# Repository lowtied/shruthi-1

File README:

Shruthi-1, a digital/analog hybrid MIDI monosynth.

This project is a redesign of the original Shruti-1, with a spec'ed up CPU,
and a focus on easy upgrades/modification of the analog section.
The ATMega644p allows new features in the firmware -- a larger selection of
oscillator algorithms, a bigger selection of wavetables, and a tiny sequencer.

Original developer: Emilie Gillet (emilie.o.gillet@gmail.com)

The firmware is released under a GPL3.0 license. It includes a
reimplementation of the formant synthesis algorithm used in Peter Knight's
Cantarino speech synthesizer.

The PCB layouts and schematics (in /hardware/shruthi/design/pcb)
are released under a Creative Commons cc-by-sa 3.0 license - except for some
discontinued filter boards which were released under a cc-by-nc-sa 3.0 license.

Documentation, analyses, simulations and 3D models are released under a
Creative Commons cc-by-sa 3.0 license.

PCB art:
- "saraswati" by Francois Barbut.
- "peacock_face" by Emilie Gillet.
- "radha" by Emilie Gillet.

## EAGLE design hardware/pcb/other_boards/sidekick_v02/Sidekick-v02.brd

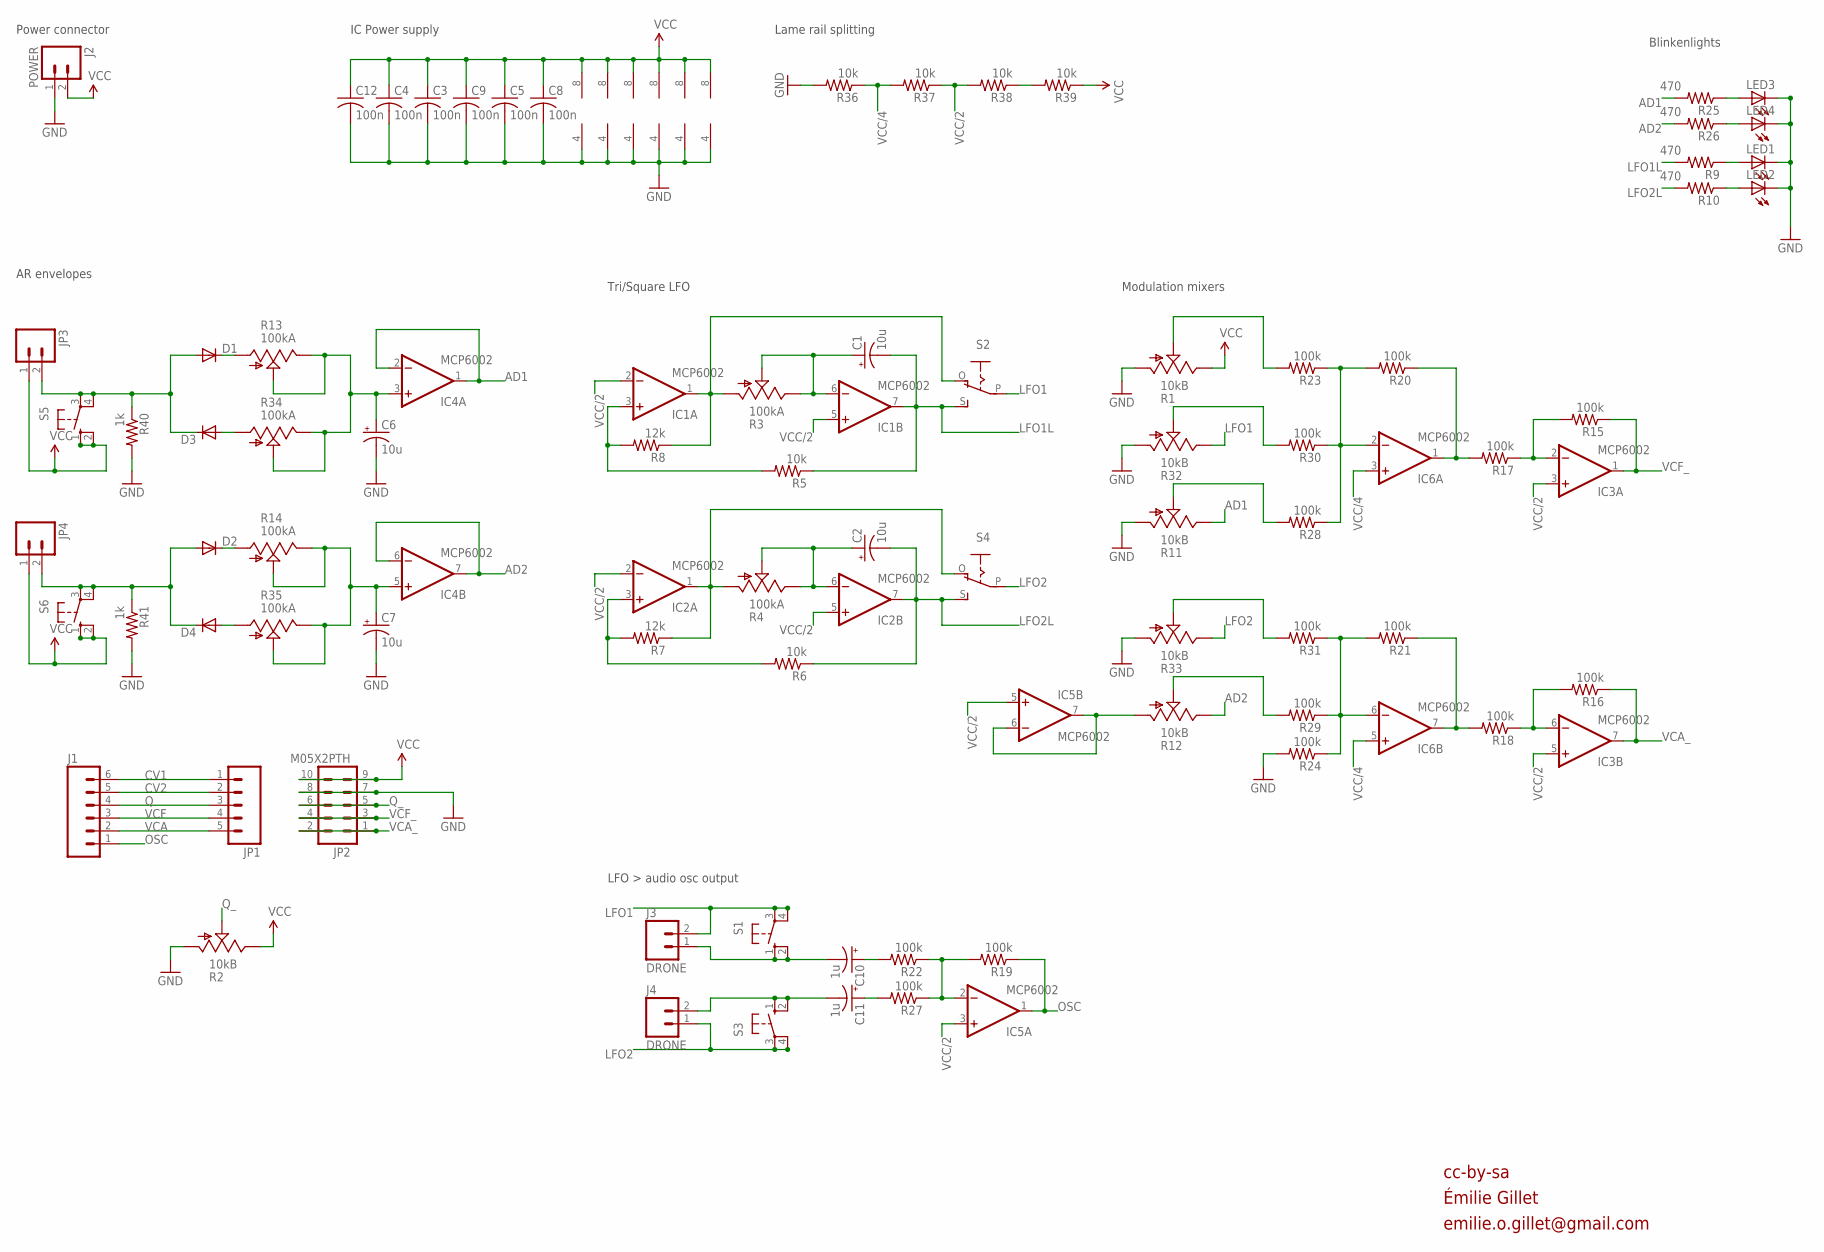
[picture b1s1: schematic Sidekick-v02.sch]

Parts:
C1, C2, C6, C7: 10u; E2,5-6
C3, C4, C5, C8, C9, C12: 100n; C025-024X044
C10, C11: 1u; E2,5-6
D1, D2, D3, D4: DIODE-D-5; D-5
IC1, IC2, IC3, IC4, IC5, IC6: MCP6002; DIL08
J1: M06SIP; 1X06
J2: POWER; 1X02
J3, J4: DRONE; 1X02
JP1: M05PTH; 1X05
JP2: M05X2PTH; AVR_ICSP
JP3, JP4: M02; 1X02_LONGPADS
LED1, LED2, LED3, LED4: LED3MM
R1, R2, R11, R12, R32, R33: 10kB; ALPS_POT_SFE
R3, R4, R13, R14, R34, R35: 100kA; ALPS_POT_SFE
R5, R6, R36, R37, R38, R39: 10k; 0204/7
R7, R8: 12k; 0204/7
R9, R10, R25, R26: 470; 0204/7
R15, R16, R17, R18, R19, R20, R21, R22, R23, R24, R27, R28, R29, R30, R31: 100k; 0204/7
R40, R41: 1k; 0204/7
S1, S3, S5, S6: 40-XX; B3F-40XX
S2, S4: EG1218S; EG1218

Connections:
AD1: IC4.1 (OUT), IC4.2 (-IN), R11.P$1 (E), R25.2
AD2: IC4.6 (-IN), IC4.7 (OUT), R12.P$1 (E), R26.2
CV1: J1.6, JP1.1
CV2: J1.5, JP1.2
GND: C3.2, C4.2, C5.2, C6.-, C7.-, C8.2, C9.2, C12.2, IC1.4 (V-), IC2.4 (V-), IC3.4 (V-), IC4.4 (V-), IC5.4 (V-), IC6.4 (V-), J2.1, JP2.7, JP2.8, LED1.K (C), LED2.K (C), LED3.K (C), LED4.K (C), R1.P$3 (A), R2.P$3 (A), R11.P$3 (A), R24.2, R32.P$3 (A), R33.P$3 (A), R36.2, R40.2, R41.2
LFO1: J3.2, R32.P$1 (E), S1.3, S1.4 (P1), S2.P
LFO1L: C1.-, IC1.7 (OUT), R5.1, R9.2, S2.S
LFO2: J4.1, R33.P$1 (E), S3.3, S3.4 (P1), S4.P
LFO2L: C2.-, IC2.7 (OUT), R6.1, R10.2, S4.S
unnamed: C11.-, J4.2, S3.1 (S), S3.2 (S1)
unnamed: D1.C, R13.P$3 (A)
unnamed: D3.A, R34.P$3 (A)
unnamed: R30.2, R32.P$2 (S)
unnamed: D2.C, R14.P$3 (A)
unnamed: D4.A, R35.P$3 (A)
unnamed: C6.+, IC4.3 (+IN), R13.P$1 (E), R13.P$2 (S), R34.P$1 (E), R34.P$2 (S)
unnamed: C7.+, IC4.5 (+IN), R14.P$1 (E), R14.P$2 (S), R35.P$1 (E), R35.P$2 (S)
unnamed: IC6.2 (-IN), R20.2, R23.1, R28.1, R30.1
unnamed: D1.A, D3.C, JP3.2, R40.1, S5.3, S5.4 (P1)
unnamed: D2.A, D4.C, JP4.2, R41.1, S6.3, S6.4 (P1)
unnamed: C1.+, IC1.6 (-IN), R3.P$1 (E), R3.P$2 (S)
unnamed: LED3.A, R25.1
unnamed: LED4.A, R26.1
unnamed: R1.P$2 (S), R23.2
unnamed: R11.P$2 (S), R28.2
unnamed: IC6.1 (OUT), R17.2, R20.1
unnamed: IC3.2 (-IN), R15.2, R17.1
unnamed: IC6.6 (-IN), R21.2, R24.1, R29.1, R31.1
unnamed: R31.2, R33.P$2 (S)
unnamed: R12.P$2 (S), R29.2
unnamed: IC1.3 (+IN), R5.2, R8.2
unnamed: IC6.7 (OUT), R18.2, R21.1
unnamed: IC3.6 (-IN), R16.2, R18.1
unnamed: IC1.1 (OUT), R3.P$3 (A), R8.1, S2.O
unnamed: IC2.3 (+IN), R6.2, R7.2
unnamed: C2.+, IC2.6 (-IN), R4.P$1 (E), R4.P$2 (S)
unnamed: IC2.1 (OUT), R4.P$3 (A), R7.1, S4.O
unnamed: IC5.2 (-IN), R19.2, R22.1, R27.1
unnamed: LED1.A, R9.1
unnamed: R38.1, R39.2
unnamed: LED2.A, R10.1
unnamed: C11.+, R27.2
unnamed: C10.+, R22.2
unnamed: C10.-, J3.1, S1.1 (S), S1.2 (S1)
NETX: IC5.6 (-IN), IC5.7 (OUT), R12.P$3 (A)
OSC: IC5.1 (OUT), J1.1, R19.1
Q: J1.4, JP1.3
Q_: JP2.5, JP2.6, R2.P$2 (S)
VCA: J1.2, JP1.5
VCA_: IC3.7 (OUT), JP2.1, JP2.2, R16.1
VCC: C3.1, C4.1, C5.1, C8.1, C9.1, C12.1, IC1.8 (V+), IC2.8 (V+), IC3.8 (V+), IC4.8 (V+), IC5.8 (V+), IC6.8 (V+), J2.2, JP2.9, JP2.10, JP3.1, JP4.1, R1.P$1 (E), R2.P$1 (E), R39.1, S5.1 (S), S5.2 (S1), S6.1 (S), S6.2 (S1)
VCC/2: IC1.2 (-IN), IC1.5 (+IN), IC2.2 (-IN), IC2.5 (+IN), IC3.3 (+IN), IC3.5 (+IN), IC5.3 (+IN), IC5.5 (+IN), R37.1, R38.2
VCC/4: IC6.3 (+IN), IC6.5 (+IN), R36.1, R37.2
VCF: J1.3, JP1.4
VCF_: IC3.1 (OUT), JP2.3, JP2.4, R15.1

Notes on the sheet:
Power connector
cc-by-sa
Émilie Gillet
emilie.o.gillet@gmail.com
Lame rail splitting
AR envelopes
Tri/Square LFO
Modulation mixers
Blinkenlights
IC Power supply
LFO > audio osc output

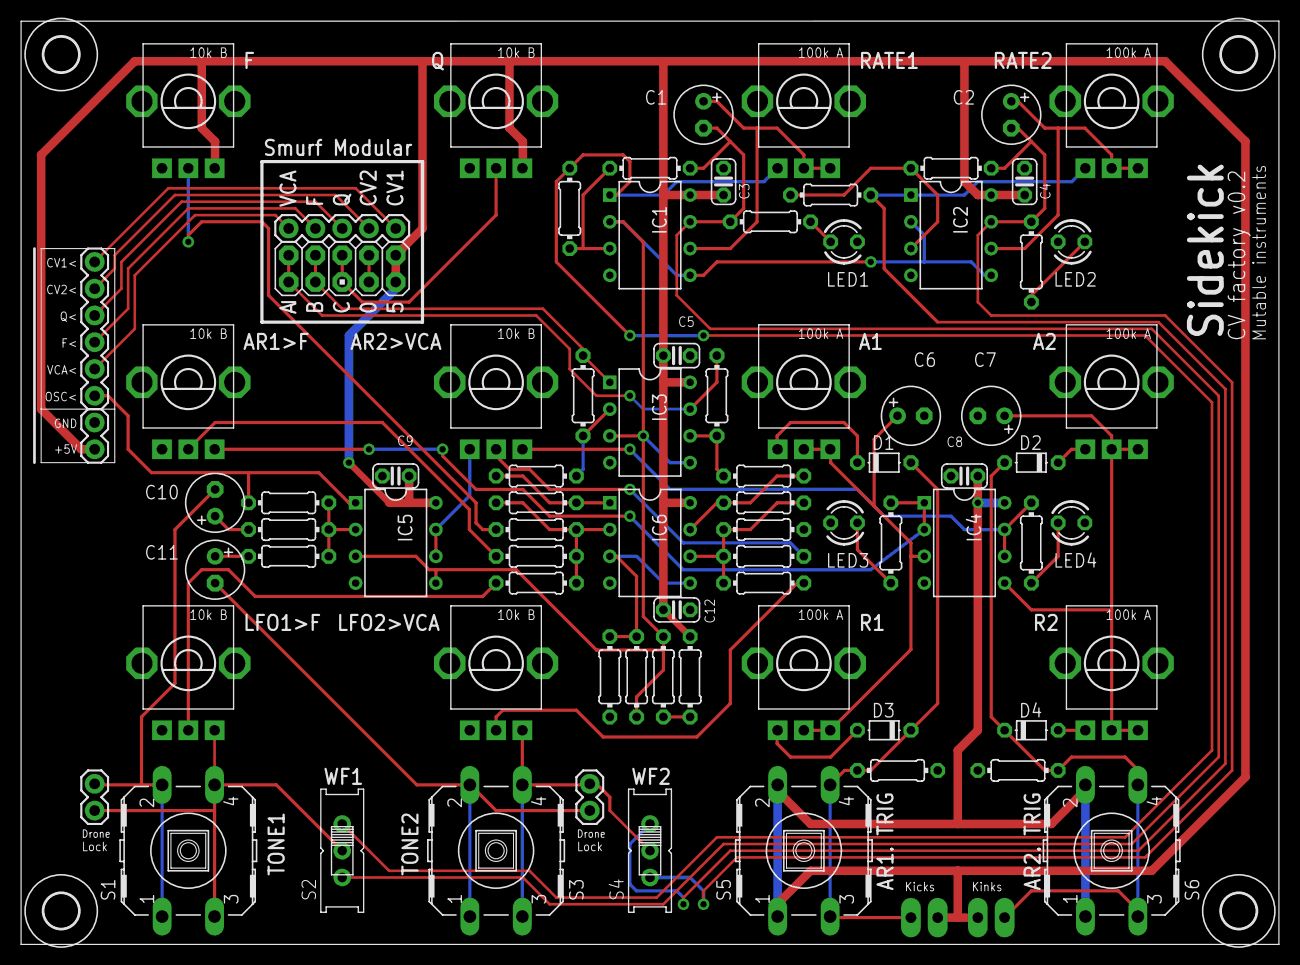
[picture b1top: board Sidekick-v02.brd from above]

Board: 2 copper layers, 119.4 x 87.6 mm, 87 parts (0 on the bottom side), 55 nets.

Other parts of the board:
U$1: ORNAMENT_1
U$2: SARASWATI
U$100, U$101, U$102, U$103: 3,3

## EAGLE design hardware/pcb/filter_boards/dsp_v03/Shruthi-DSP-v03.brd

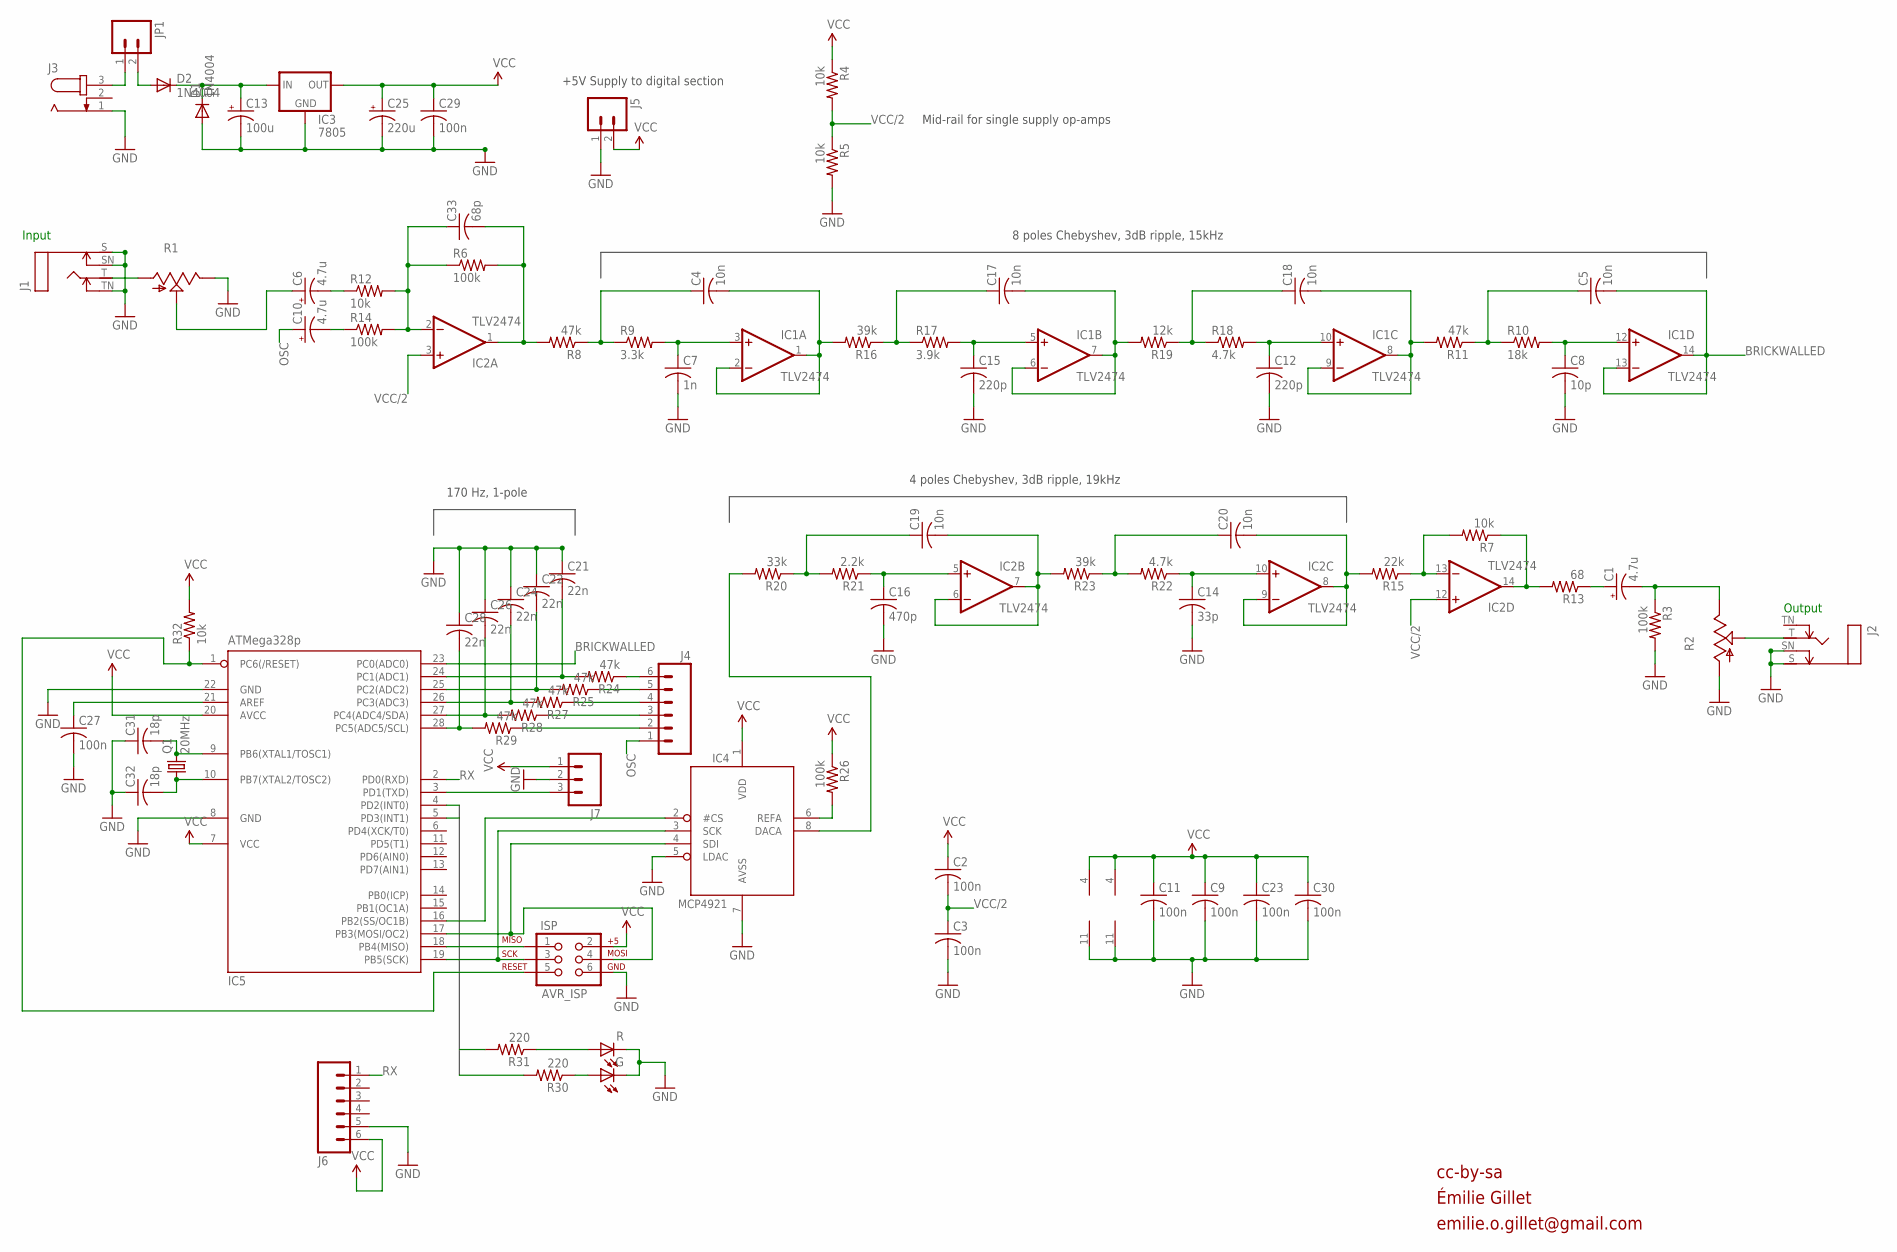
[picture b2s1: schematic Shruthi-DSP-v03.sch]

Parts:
C1, C6, C10: 4.7u; E2,5-6
C2, C3, C30: 100n; C025-024X044
C4, C5, C17, C18, C19, C20: 10n; C050-025X075
C7: 1n; C025-025X050
C8: 10p; C025-025X050
C9, C11, C23, C27, C29: 100n; C025-025X050
C12, C15: 220p; C025-025X050
C13: 100u; E2,5-7
C14: 33p; C025-025X050
C16: 470p; C025-025X050
C21, C22, C24, C26, C28: 22n; C050-025X075
C25: 220u; E5-10,5
C31, C32: 18p; C025-024X044
C33: 68p; C025-025X050
D1, D2: 1N4004; DO41-10
G: LED3MM
IC1, IC2: TLV2474; DIL14
IC3: 7805; 78XXS
IC4: MCP4921; DIL08
IC5: ATMega328p; DIL28-3
ISP: AVR_ISP; 2X3
J1, J2: MONOSWS; NMJ4HC-S
J3: JACK-PLUG2; SPC4078_BIG_HOLES
J4, J6: M06SIP; 1X06
J5: M02PTH; 1X02
J7: M03PTH; 1X03
JP1: M02; 1X02_LONGPADS
Q1: 20MHz; HC49U-V
R: LED3MM
R1, R2: POT_USCABLED; CABLE_POT_6MM
R3, R6, R14, R26: 100k; 0204/7
R4, R5, R7, R12, R32: 10k; 0204/7
R8, R11, R24, R25, R27, R28, R29: 47k; 0204/7
R9: 3.3k; 0204/7
R10: 18k; 0204/7
R13: 68; 0204/7
R15: 22k; 0204/7
R16, R23: 39k; 0204/7
R17: 3.9k; 0204/7
R18, R22: 4.7k; 0204/7
R19: 12k; 0204/7
R20: 33k; 0204/7
R21: 2.2k; 0204/7
R30, R31: 220; 0204/7

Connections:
BRICKWALLED: C5.2, IC1.13 (-IN), IC1.14 (OUT), IC5.23 (PC0(ADC0))
GND: C3.2, C7.2, C8.2, C9.2, C11.2, C12.2, C13.-, C14.2, C15.2, C16.2, C21.1, C22.1, C23.2, C24.1, C25.-, C26.1, C27.2, C28.1, C29.2, C30.2, C31.1, C32.1, D1.A, G.K (C), IC1.11 (V-), IC2.11 (V-), IC3.GND, IC4.5 (LDAC), IC4.7 (AVSS), IC5.8 (GND), IC5.22 (GND), ISP.6, J1.S, J1.SN, J1.TN, J2.S, J2.SN, J3.1, J5.1, J6.5, J7.2, R.K (C), R1.E, R2.A, R3.2, R5.2
LEDS0: IC5.4 (PD2(INT0)), R31.2
LEDS1: IC5.5 (PD3(INT1)), R30.2
unnamed: C7.1, IC1.3 (+IN), R9.2
unnamed: C4.1, R8.1, R9.1
unnamed: J3.3, JP1.1
unnamed: C13.+, D1.C, D2.C, IC3.IN
unnamed: C4.2, IC1.1 (OUT), IC1.2 (-IN), R16.2
unnamed: C15.1, IC1.5 (+IN), R17.2
unnamed: C17.1, R16.1, R17.1
unnamed: C17.2, IC1.6 (-IN), IC1.7 (OUT), R19.2
unnamed: C12.1, IC1.10 (+IN), R18.2
unnamed: C18.1, R18.1, R19.1
unnamed: C18.2, IC1.8 (OUT), IC1.9 (-IN), R11.2
unnamed: C8.1, IC1.12 (+IN), R10.2
unnamed: C5.1, R10.1, R11.1
unnamed: IC5.1 (PC6(/RESET)), ISP.5, R32.1
unnamed: C27.1, IC5.21 (AREF)
unnamed: IC4.6 (REFA), R26.2
unnamed: IC5.18 (PB4(MISO)), ISP.1
unnamed: IC4.3 (SCK), IC5.19 (PB5(SCK)), ISP.3
unnamed: C6.+, R1.S
unnamed: IC4.4 (SDI), IC5.17 (PB3(MOSI/OC2)), ISP.4
unnamed: J1.T, R1.A
unnamed: IC4.2 (#CS), IC5.16 (PB2(SS/OC1B))
unnamed: C19.1, R20.1, R21.2
unnamed: C6.-, R12.1
unnamed: C16.1, IC2.5 (+IN), R21.1
unnamed: C19.2, IC2.6 (-IN), IC2.7 (OUT), R23.2
unnamed: J4.2, R29.1
unnamed: C20.1, R22.2, R23.1
unnamed: C14.1, IC2.10 (+IN), R22.1
unnamed: C20.2, IC2.8 (OUT), IC2.9 (-IN), R15.2
unnamed: IC4.8 (DACA), R20.2
unnamed: C1.-, R2.E, R3.1
unnamed: C10.-, R14.1
unnamed: IC2.13 (-IN), R7.2, R15.1
unnamed: IC2.14 (OUT), R7.1, R13.2
unnamed: C1.+, R13.1
unnamed: IC5.3 (PD1(TXD)), J7.3
unnamed: C33.1, IC2.2 (-IN), R6.1, R12.2, R14.2
unnamed: J2.T, R2.S
unnamed: C33.2, IC2.1 (OUT), R6.2, R8.2
unnamed: J4.3, R28.1
unnamed: J4.4, R27.1
unnamed: J4.5, R25.1
unnamed: J4.6, R24.1
unnamed: C28.2, IC5.28 (PC5(ADC5/SCL)), R29.2
unnamed: C26.2, IC5.27 (PC4(ADC4/SDA)), R28.2
unnamed: C24.2, IC5.26 (PC3(ADC3)), R27.2
unnamed: C22.2, IC5.25 (PC2(ADC2)), R25.2
unnamed: C21.2, IC5.24 (PC1(ADC1)), R24.2
unnamed: R.A, R31.1
unnamed: G.A, R30.1
unnamed: D2.A, JP1.2
unnamed: C32.2, IC5.10 (PB7(XTAL2/TOSC2)), Q1.1
unnamed: C31.2, IC5.9 (PB6(XTAL1/TOSC1)), Q1.2
OSC: C10.+, J4.1
RX: IC5.2 (PD0(RXD)), J6.1
VCC: C2.1, C9.1, C11.1, C23.1, C25.+, C29.1, C30.1, IC1.4 (V+), IC2.4 (V+), IC3.OUT, IC4.1 (VDD), IC5.7 (VCC), IC5.20 (AVCC), ISP.2, J5.2, J6.6, J7.1, R4.1, R26.1, R32.2
VCC/2: C2.2, C3.1, IC2.3 (+IN), IC2.12 (+IN), R4.2, R5.1

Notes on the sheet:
+5V Supply to digital section
Input
Output
cc-by-sa
Émilie Gillet
emilie.o.gillet@gmail.com
Mid-rail for single supply op-amps
8 poles Chebyshev, 3dB ripple, 15kHz
4 poles Chebyshev, 3dB ripple, 19kHz
170 Hz, 1-pole

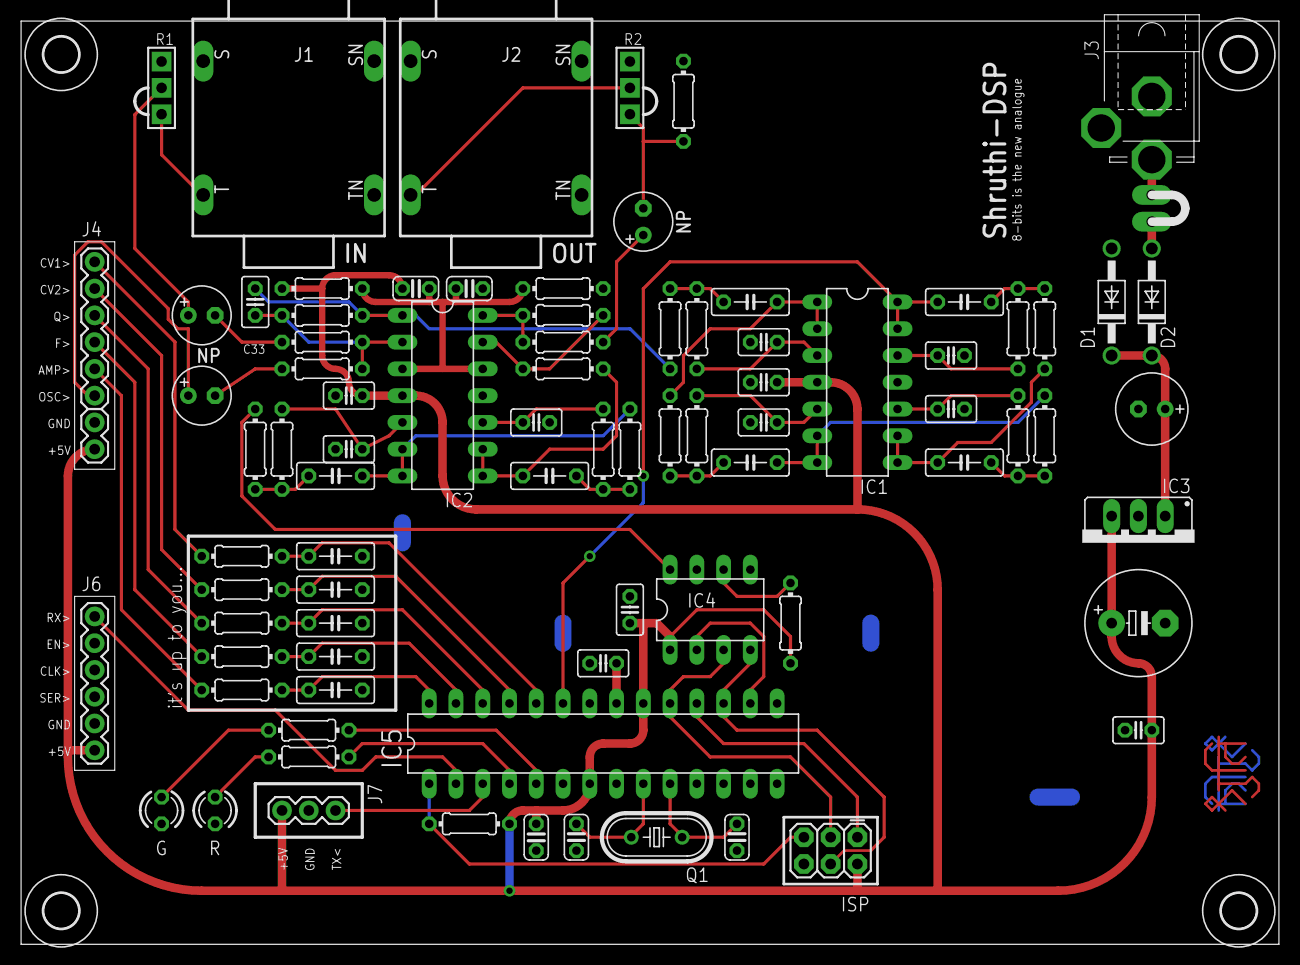
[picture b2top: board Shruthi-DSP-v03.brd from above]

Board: 2 copper layers, 119.4 x 87.6 mm, 90 parts (0 on the bottom side), 62 nets.

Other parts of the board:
U$1, U$2, U$5, U$6: 3,3
U$3: RANGOLI
U$4: DURGA2

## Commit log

2025-06-11 update git submodules
2025-06-11 move graphics into resources directory and move art credits to main readme
2025-06-11 move graphic from dsp board into resources folder
2025-06-11 move boards into seperate folders, remove uneeded boards
2025-06-11 move enclosure design files to enclosure directory
2025-06-11 move documentation files into docs folder
2025-06-11 move source files and folders to firmware folder
2025-06-11 remove v02 svf filter board due to errors in eagle project
2025-06-11 update all eagle projects to latest versions
2025-06-11 update gitignore
2025-06-11 import eagle project into kicad
2025-06-17 center q1 between r24 and r25, increase spacing between c11 and c12
2025-06-17 add mounting hole footprint
2025-06-17 use new mounting hole footprint
2025-06-17 remove extra worksheet frame
2025-06-17 update capacitors to use kicad symbols
2025-06-17 update jumpers to use kicad symbols
2025-06-19 update crystal to use kicad symbols
2025-06-19 update vcc to use kicad symbols
2025-06-19 update gnd to use kicad symbols
2025-06-19 update resistors to use kicad symbols
2025-06-19 update atmega644p to use kicad symbols
2025-06-20 add atmega644p datasheet
2025-06-20 use relative path for footprints library
2025-06-20 move libraries directory to root of repository
2025-06-20 move enclosure files to cad directory
2025-06-20 update 24LC512 to use kicad symbols
2025-06-20 remove sidekick board
2025-06-20 update AVR ISP to use kicad symbols
2025-06-20 update MIDI circuitry to use kicad symbols
2025-06-20 move bypass capacitors next to respective devices
2025-06-23 fix footprint library location
2025-06-23 update footprints for atmega and 6N137
2025-06-23 add datasheet for 4051
2025-06-23 update 4051 to use kicad symbols
2025-06-23 update 4051 footprints
2025-06-23 update pots to use kicad symbols
2025-06-23 remove aligment lines from User.4 layer
2025-06-23 fix pin numbering for pot footprint
2025-06-23 update volume jumpers to use kicad symbols
2025-06-23 update 75HC165s to use kicad symbols
2025-06-23 update resistor networks to use kicad symbols
2025-06-23 add SN74HC165 datasheet
2025-06-23 fix extra connections on IC2
2025-06-23 update switches to use kicad symbols
2025-06-23 update footprints on pcb and fix a few minor errors
2025-06-23 remove top fill zone and replace bottom fill zone
2025-06-23 update 74HC165 footprints
2025-06-23 update 74HC595 and LED symbols
2025-06-23 remove loose wires and text
2025-06-23 update LCD parts to use kicad symbols
2025-06-23 use original LCD footprint for now
2025-06-24 use 1x8 header instead of separate ones for J1 and J2
2025-06-24 update position of board to board connectors
2025-06-24 update LED and LED resistor footprints
2025-06-24 update footprint for 74HC595
2025-06-24 update silkscreen for 74HC165s
2025-06-24 update silkscreen for 4051s
2025-06-24 update footprint and silkscreen for volume jumpers
2025-06-24 update footprint and silkscreen for isp header
2025-06-24 update footprints and silkscreen for optocoupler circuitry
2025-06-24 add 24LC512 datasheet
2025-06-24 update footprints and silkscreen for 24LC512 circuitry
2025-06-24 update footprints and silkscreen for big cap
2025-06-24 ignore file that tracks autosave files
2025-06-24 remove imported eagle symbols
2025-06-30 remove files related to everything except shruthi-xt
2025-06-30 consolidate files related to shruthi-xt into flatter structure
2025-06-30 rename control board kicad project
2025-06-30 rename sheets
2025-06-30 update symbol and footprint for display
2025-06-30 update lcd LED and trimmer footprints
2025-06-30 move midi components to daughterboard
2025-07-01 move all logic components to daughterboard, move MIDI to new board
